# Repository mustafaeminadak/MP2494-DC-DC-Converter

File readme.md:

# MP2494 DC-DC Converter

This repository contains the hardware design files for a **DC/DC Buck Converter** based on the **MP2494 Step-Down Regulator IC**. The design focuses on **Low EMI**, **High Efficiency**, and **Reliable PCB Layout Practices** to ensure stable operation. You will find resources such as datasheets, specifications, design considerations, schematics, layouts, and 3D previews of the board.  

## 📑 Datasheet  

The MP2494 is a **monolithic step-down switch mode converter**. It delivers up to **2A continuous output current** across a wide input voltage range with excellent load and line regulation.  

- Features low EMI signature with controlled switching edges.  
- Built-in protections: **cycle-by-cycle current limiting** and **thermal shutdown**.  
- Requires only a few standard external components.  
- Available in **SOIC8** and **SOIC8E** packages.  

The MP2494 uses a **current-mode control architecture**:  
- At the start of a cycle, the switch turns on, connecting the inductor to the input supply.  
- The inductor current is sensed and compared with the Error Amplifier output.  
- When the sensed current exceeds the control threshold, the switch is turned off.  
- A Schottky diode carries inductor current during the off cycle.  

##

## ⚙️ Specifications

* Input Voltage Range: **10V – 48V**
* Nominal Voltage: **12V**
* Output Voltage: **5V**
* Output Current: **2A**
* Switching Frequency: **100kHz (typical)**
* Inductor Ripple Current: **38%**
* Slew Rate of Transient: **1 A/µs**
* Protection: **OCP, Thermal Shutdown**
* Efficiency (measured): **~85.75%**

# MPS Design Tool Simulation

## 🛠️ Design Considerations

When designing the PCB, follow these layout guidelines for stable operation and reduced EMI:

1. Place the **input capacitor** and **freewheel diode** on the same PCB layer as the IC and as close as possible to the IC pins.
2. Use **thermal vias** if necessary to improve heat dissipation.
3. Place the **inductor close to the IC**, but it does not need to be as close as the input capacitor. Keep copper area for the switching node minimal to reduce noise radiation.
4. Place the **output capacitor close to the inductor**.
5. Keep the **ground return path** away from noise-sensitive components.

Additional Notes:

* For mounting holes, GND connection depends on mechanical and shielding needs.
* Edge plating is not required for all boards but can help in high-current, EMI-sensitive designs.
* The EN pin can be tied to VIN (always-on) or controlled via a resistor divider (optional R7).

##

##

## 📐 Schematic

## 🧩 Layout

##

##

## 🎨 3D View

##

## 📌 Notes

* Efficiency achieved: **~85.75%** (very good for this design).
* Mounting hole GND connection is optional, depending on mechanical and EMI needs.
* R7 is optional: if EN pin should be always active, tie directly to VIN.
* Edge plating is not mandatory unless your design requires **high shielding or structural robustness**.

## 🏭 Manufacturing

The PCB for this project can be fabricated using standard FR4 process.  
Gerber files are provided in the repository for direct upload to PCB manufacturers.

For interactive inspection of the Gerber layers, you can use **PCBWay Online Gerber Viewer**:  

Simply click the button above and upload the provided Gerber `.zip` file to view all PCB layers online.

##

## 📜 License 
This project is released under the MIT License.

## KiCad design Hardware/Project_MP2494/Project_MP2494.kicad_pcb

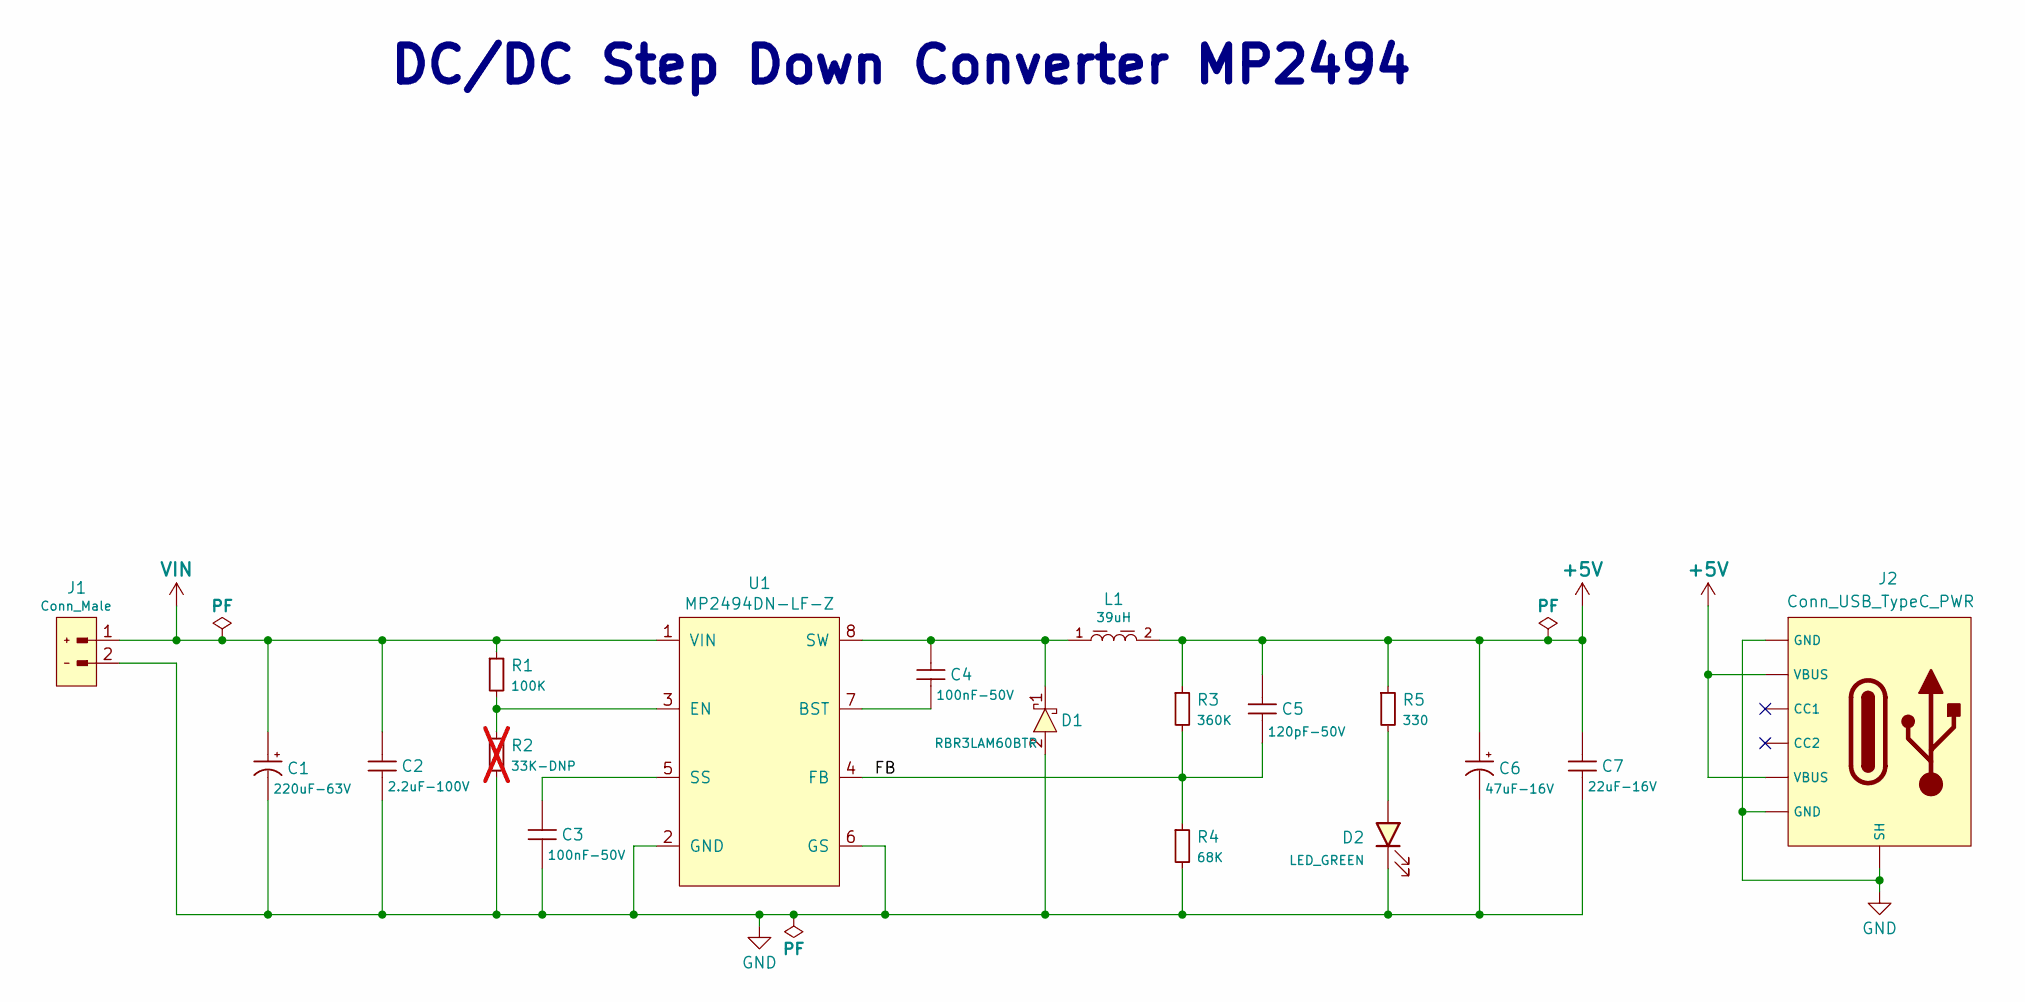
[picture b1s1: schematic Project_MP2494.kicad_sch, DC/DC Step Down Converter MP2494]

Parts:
C1: 220uF-63V; WCAP-ASLI_12.5X14_DXL_220U_; Part Number 865080762015
C2: 2.2uF-100V; C_1206_3216Metric_Pad1.33x1.80mm_HandSolder; Part Number CC1206KKX7R0BB225
C3, C4: 100nF-50V; C_0603_1608Metric_Pad1.08x0.95mm_HandSolder; Part Number C0603C104K5RACTU
C5: 120pF-50V; C_0603_1608Metric_Pad1.08x0.95mm_HandSolder; Part Number C0603C121K5RACAUTO
C6: 47uF-16V; WCAP-ASLI_5X5.5_DXL_47U_; Part Number 865080342006
C7: 22uF-16V; C_0805_2012Metric_Pad1.18x1.45mm_HandSolder; Part Number CC0805MKX5R7BB226
D1: RBR3LAM60BTR; DIO_RB050LAM_ROM-M
D2: LED_GREEN; LED_0805_2012Metric_Pad1.15x1.40mm_HandSolder
J1: Conn_Male; AMASS_XT60PW-M; Part Number XT60PW-M
J2: Conn_USB_TypeC_PWR; 2171750001_MOL; Part Number 2171750001
L1: 39uH; WE-PD_1210
R1: 100K; R_0805_2012Metric_Pad1.20x1.40mm_HandSolder
R2: 33K-DNP; R_0805_2012Metric_Pad1.20x1.40mm_HandSolder; not fitted
R3: 360K; R_0805_2012Metric_Pad1.20x1.40mm_HandSolder
R4: 68K; R_0805_2012Metric_Pad1.20x1.40mm_HandSolder
R5: 330; R_0805_2012Metric_Pad1.20x1.40mm_HandSolder
U1: MP2494DN-LF-Z; SOIC8E

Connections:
+5V: C5.1, C6.1, C7.1, J2.A9 (VBUS), J2.B9 (VBUS), L1.2, R3.1, R5.1
/FB: C5.2, R3.2, R4.1, U1.4 (FB)
GND: C1.2, C2.2, C3.1, C6.2, C7.2, D1.2 (A), D2.1 (K), J1.2, J2.7 (SH), J2.A12 (GND), J2.B12 (GND), R2.2, R4.2, U1.2 (GND), U1.6 (GS)
unnamed: C4.2, D1.1 (C), L1.1, U1.8 (SW)
unnamed: D2.2 (A), R5.2
unnamed: C4.1, U1.7 (BST)
unnamed: R1.2, R2.1, U1.3 (EN)
unnamed: C3.2, U1.5 (SS)
VIN: C1.1, C2.1, J1.1, R1.1, U1.1 (VIN)

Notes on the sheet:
DC/DC Step Down Converter MP2494

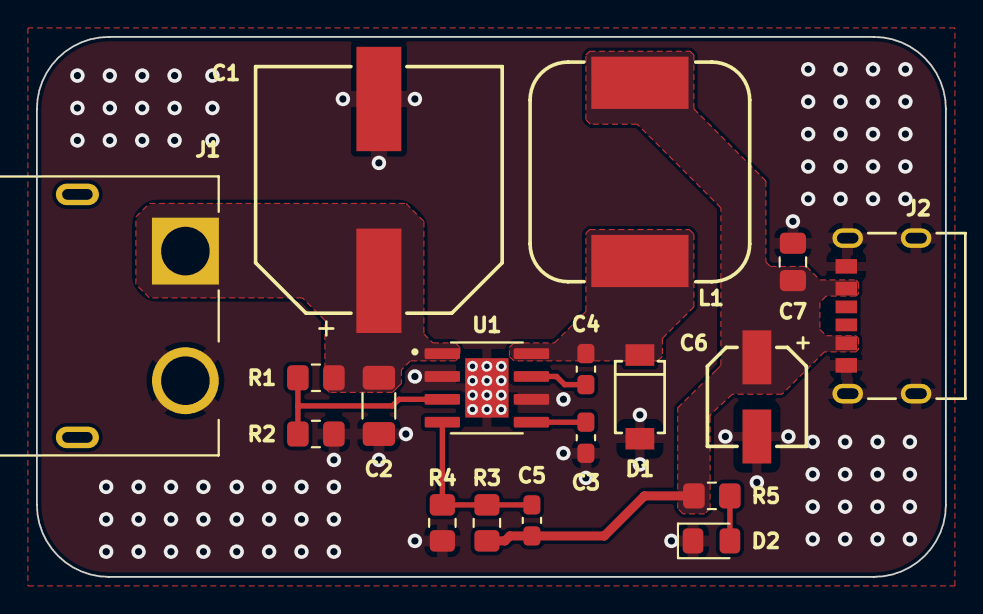
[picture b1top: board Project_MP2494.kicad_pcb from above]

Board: 2 copper layers, 50.5 x 30.0 mm, 18 parts (0 on the bottom side), 9 nets.

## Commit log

2025-09-28 MP2494-DC-DC-Converter
2025-09-28 readme.md
